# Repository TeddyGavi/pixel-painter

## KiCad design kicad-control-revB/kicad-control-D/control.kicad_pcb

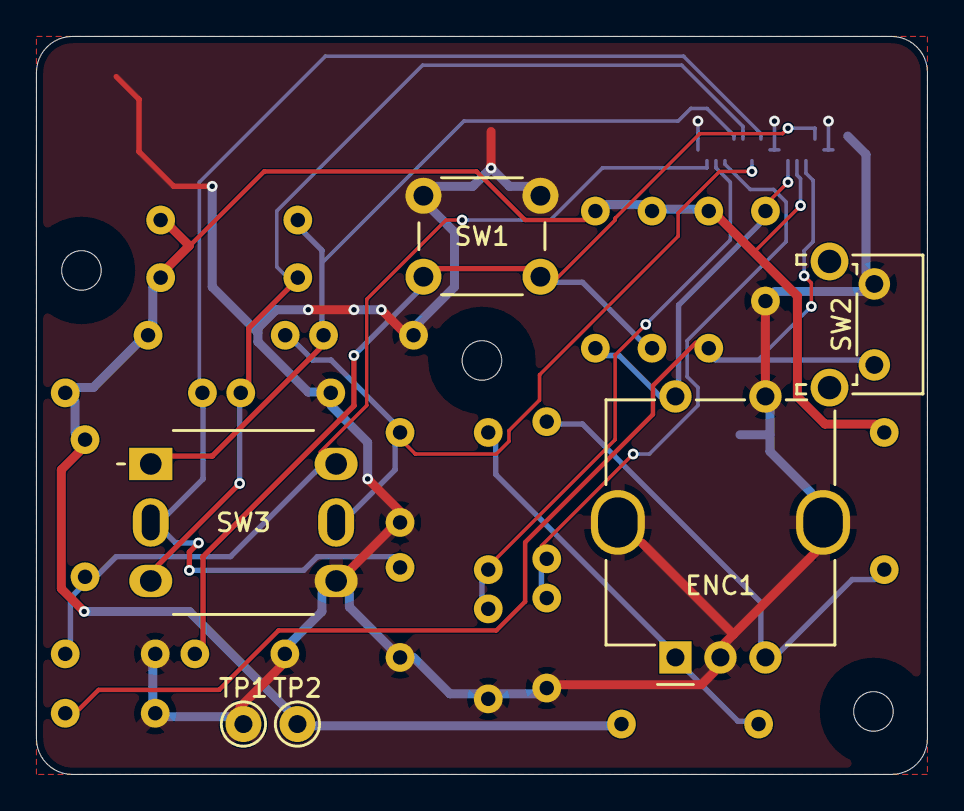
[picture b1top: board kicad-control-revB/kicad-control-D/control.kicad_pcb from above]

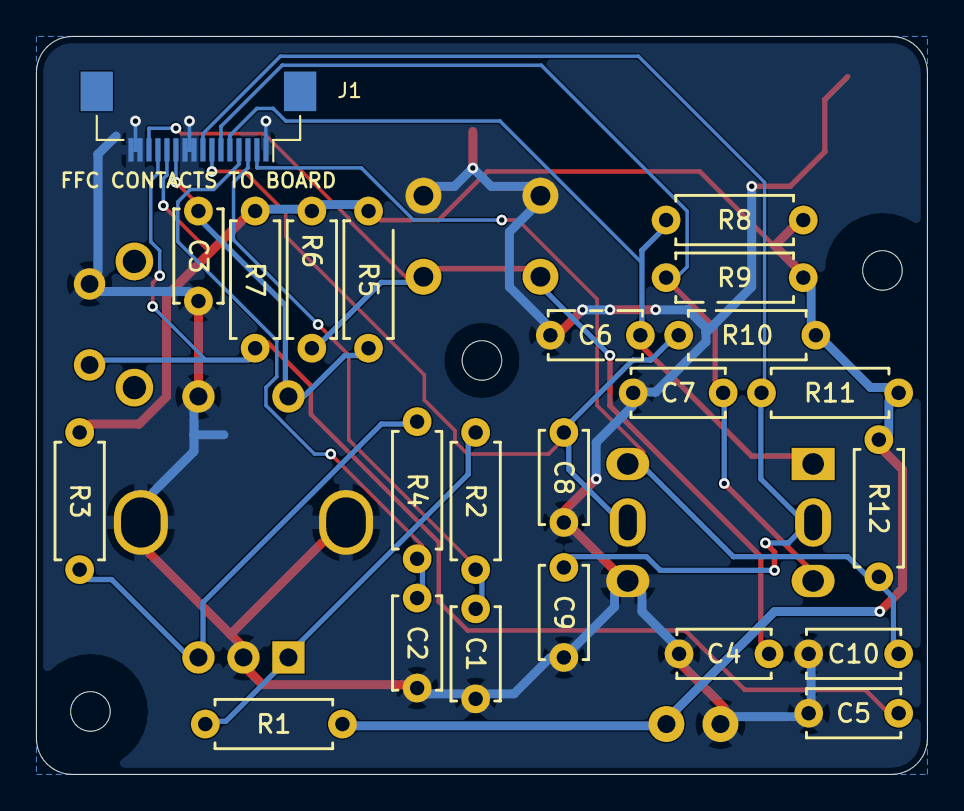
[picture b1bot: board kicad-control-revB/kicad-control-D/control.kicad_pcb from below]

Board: 2 copper layers, 49.5 x 41.0 mm, 32 parts (23 on the bottom side), 14 nets.

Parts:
C1, C2, C3, C4, C5, C6, C7, C8, C9, C10: 10nF; C_Disc_D5.0mm_W2.5mm_P5.00mm
ENC1: PEC11R-4215F-S0024; RotaryEncoder_Bourns_PEC11R-4xxxF-Sxxxx_Vertical
H1, H2, H3: M2; MountingHole_2.2mm_M2
J1: FH12-16S-0.5SH(55); Hirose_FH12-16S-0.5SH_1x16-1MP_P0.50mm_Horizontal
R1, R2, R3, R4, R5, R6, R7, R8, R9, R10, R11, R12: 10k; R_Axial_DIN0207_L6.3mm_D2.5mm_P7.62mm_Horizontal
SW1: B3F-1000 (MENU); SW_PUSH_6mm
SW2: PTS645VL31-2 LFS (SIDE); SW_Tactile_SPST_Angled_PTS645Vx31-2LFS
SW3: SKQUCAA010; SW_Alps_SKQUCAA010_5way_THT
TP1: GND; TestPoint_THTPad_D2.0mm_Drill1.0mm
TP2: 3V3; TestPoint_THTPad_D2.0mm_Drill1.0mm

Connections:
+3V3: J1.12, R1.1, R3.1, R5.1, R6.1, R7.1, R8.1, R9.1, R10.1, R11.1, R12.1, TP2.1
/BTN_MENU: C4.1, J1.14, R6.2, SW1.2
/BTN_SIDE: C5.1, J1.13, R7.2, SW2.2
/ENC_A: C1.1, J1.3, R2.2
/ENC_A_RAW: ENC1.A, R1.2, R2.1
/ENC_B: C2.1, J1.4, R4.2
/ENC_B_RAW: ENC1.B, R3.2, R4.1
/ENC_SW: C3.1, ENC1.S1, J1.11, R5.2
/NAV_C: C10.1, J1.2, R12.2, SW3.6
/NAV_DOWN: C7.1, J1.6, R9.2, SW3.3
/NAV_LEFT: C8.1, J1.7, R10.2, SW3.5
/NAV_RIGHT: C9.1, J1.8, R11.2, SW3.2
/NAV_UP: C6.1, J1.5, R8.2, SW3.1
GND: C1.2, C2.2, C3.2, C4.2, C5.2, C6.2, C7.2, C8.2, C9.2, C10.2, ENC1.C, ENC1.MP, ENC1.S2, J1.1, J1.9, J1.10, J1.15, J1.16, SW1.1, SW2.1, SW3.4, TP1.1

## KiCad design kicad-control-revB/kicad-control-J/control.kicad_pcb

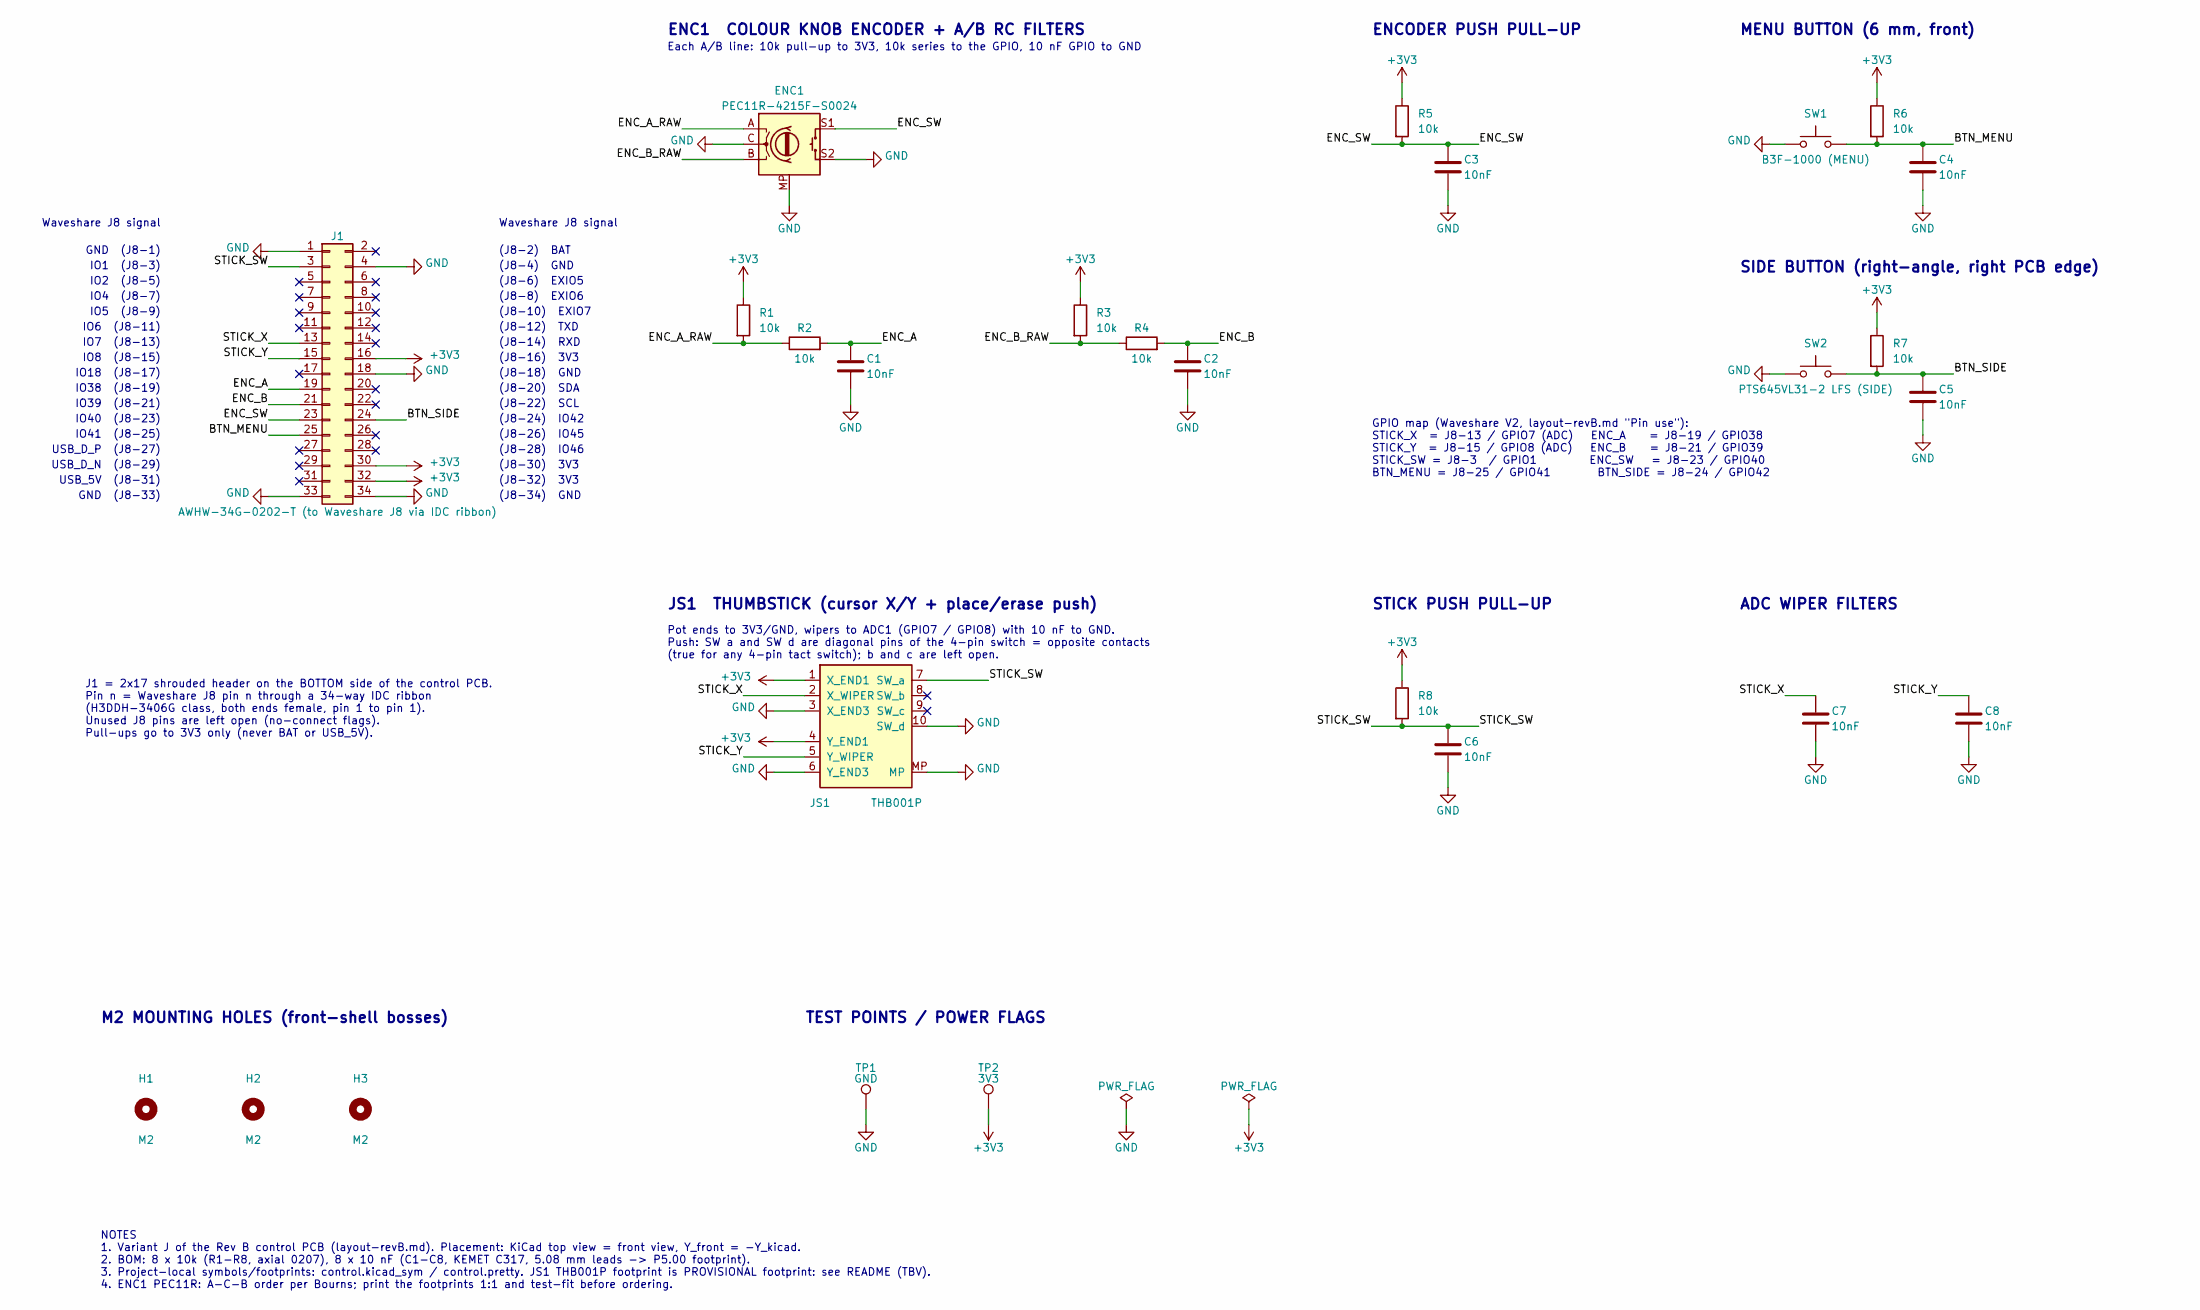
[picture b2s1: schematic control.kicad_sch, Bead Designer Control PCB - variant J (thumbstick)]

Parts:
C1, C2, C3, C4, C5, C6, C7, C8: 10nF; C_Disc_D5.0mm_W2.5mm_P5.00mm; MPN C317C103K5R5TA
ENC1: PEC11R-4215F-S0024; RotaryEncoder_Bourns_PEC11R-4xxxF-Sxxxx_Vertical; MPN PEC11R-4215F-S0024
H1, H2, H3: M2; MountingHole_2.2mm_M2; MPN N/A (PCB hole, M2 screw)
J1: AWHW-34G-0202-T (to Waveshare J8 via IDC ribbon); IDC-Header_2x17_P2.54mm_Vertical; MPN AWHW-34G-0202-T
JS1: THB001P; Joystick_CK_THB001P_PROVISIONAL; MPN THB001P
R1, R2, R3, R4, R5, R6, R7, R8: 10k; R_Axial_DIN0207_L6.3mm_D2.5mm_P7.62mm_Horizontal; MPN MFR-25FRF52-10K
SW1: B3F-1000 (MENU); SW_PUSH_6mm; MPN B3F-1000
SW2: PTS645VL31-2 LFS (SIDE); SW_Tactile_SPST_Angled_PTS645Vx31-2LFS; MPN PTS645VL31-2 LFS
TP1: GND; TestPoint_THTPad_D2.0mm_Drill1.0mm; MPN N/A (bare THT pad)
TP2: 3V3; TestPoint_THTPad_D2.0mm_Drill1.0mm; MPN N/A (bare THT pad)

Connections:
+3V3: J1.16, J1.30, J1.32, JS1.1 (X_END1), JS1.4 (Y_END1), R1.1, R3.1, R5.1, R6.1, R7.1, R8.1, TP2.1
/BTN_MENU: C4.1, J1.25, R6.2, SW1.2
/BTN_SIDE: C5.1, J1.24, R7.2, SW2.2
/ENC_A: C1.1, J1.19, R2.2
/ENC_A_RAW: ENC1.A, R1.2, R2.1
/ENC_B: C2.1, J1.21, R4.2
/ENC_B_RAW: ENC1.B, R3.2, R4.1
/ENC_SW: C3.1, ENC1.S1, J1.23, R5.2
/STICK_SW: C6.1, J1.3, JS1.7 (SW_a), R8.2
/STICK_X: C7.1, J1.13, JS1.2 (X_WIPER)
/STICK_Y: C8.1, J1.15, JS1.5 (Y_WIPER)
GND: C1.2, C2.2, C3.2, C4.2, C5.2, C6.2, C7.2, C8.2, ENC1.C, ENC1.MP, ENC1.S2, J1.1, J1.4, J1.18, J1.33, J1.34, JS1.3 (X_END3), JS1.6 (Y_END3), JS1.10 (SW_d), JS1.MP, SW1.1, SW2.1, TP1.1

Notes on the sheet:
Waveshare J8 signal
GND (J8-1)
(J8-2) BAT
IO1 (J8-3)
(J8-4) GND
IO2 (J8-5)
(J8-6) EXIO5
IO4 (J8-7)
(J8-8) EXIO6
IO5 (J8-9)
(J8-10) EXIO7
IO6 (J8-11)
(J8-12) TXD
IO7 (J8-13)
(J8-14) RXD
IO8 (J8-15)
(J8-16) 3V3
IO18 (J8-17)
(J8-18) GND
IO38 (J8-19)
(J8-20) SDA
IO39 (J8-21)
(J8-22) SCL
IO40 (J8-23)
(J8-24) IO42
IO41 (J8-25)
(J8-26) IO45
USB_D_P (J8-27)
(J8-28) IO46
USB_D_N (J8-29)
(J8-30) 3V3
USB_5V (J8-31)
(J8-32) 3V3
GND (J8-33)
(J8-34) GND
J1 = 2x17 shrouded header on the BOTTOM side of the control PCB. Pin n = Waveshare J8 pin n through a 34-way IDC ribbon (H3DDH-3406G class, both ends female, pin 1 to pin 1). Unused J8 pins are left open (no-connect flags). Pull-ups go to 3V3 only (never BAT or USB_5V).
ENC1 COLOUR KNOB ENCODER + A/B RC FILTERS
Each A/B line: 10k pull-up to 3V3, 10k series to the GPIO, 10 nF GPIO to GND
ENCODER PUSH PULL-UP
MENU BUTTON (6 mm, front)

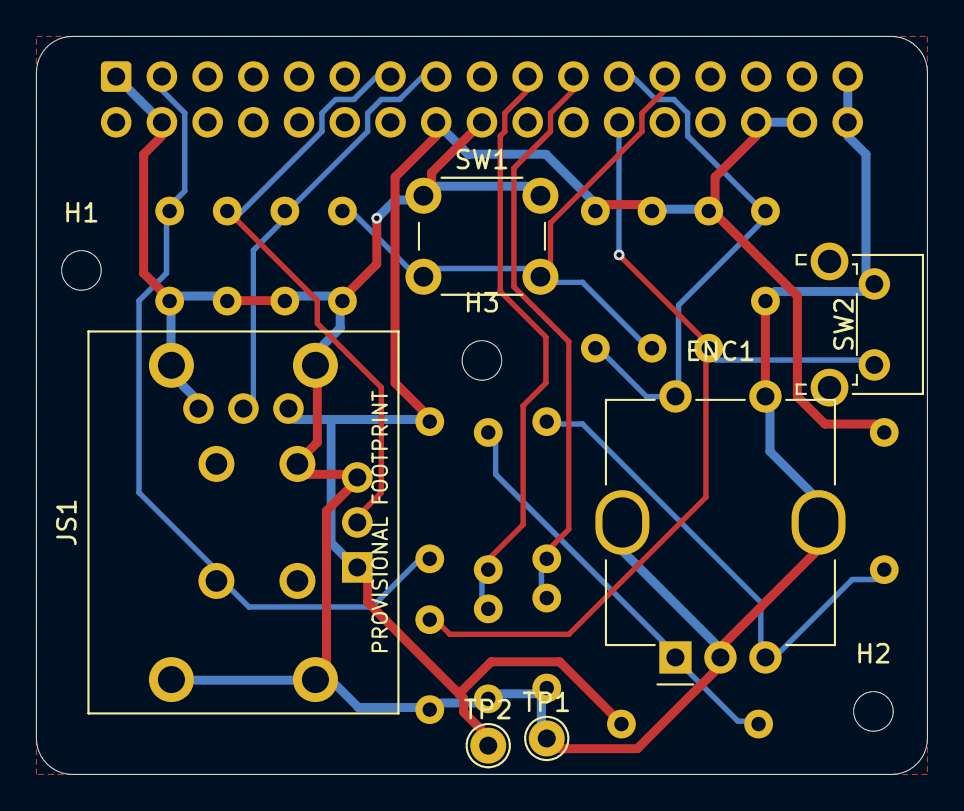
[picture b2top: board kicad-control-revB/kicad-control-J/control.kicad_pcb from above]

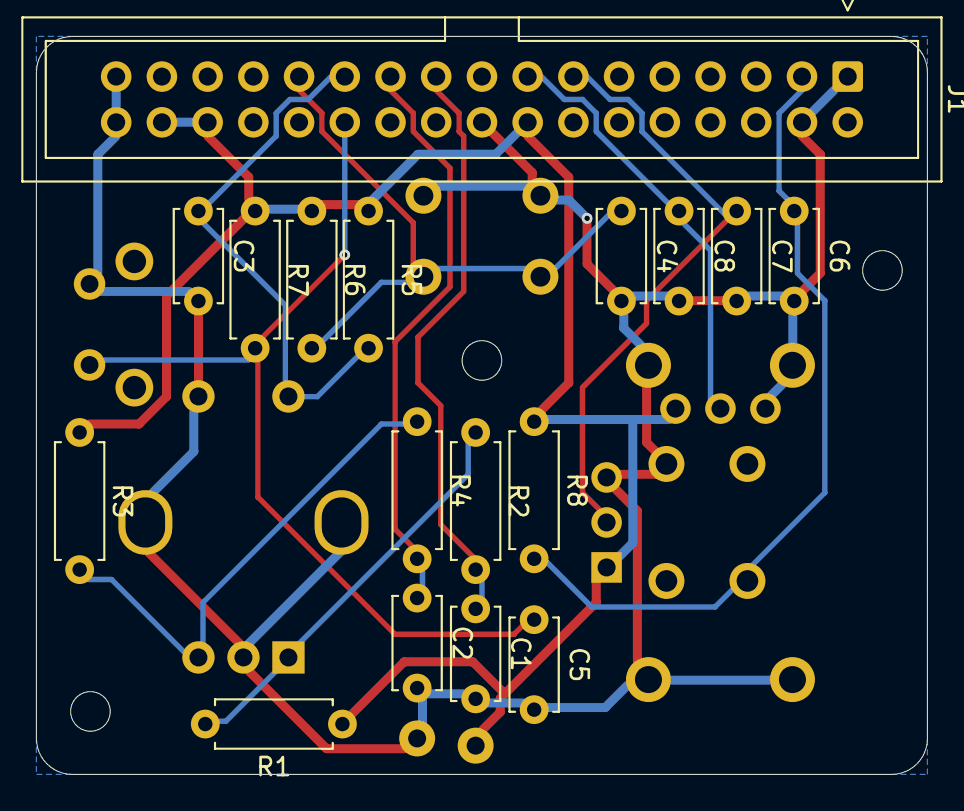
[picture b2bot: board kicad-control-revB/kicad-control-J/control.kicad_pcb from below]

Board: 2 copper layers, 49.5 x 41.0 mm, 26 parts (17 on the bottom side), 12 nets.

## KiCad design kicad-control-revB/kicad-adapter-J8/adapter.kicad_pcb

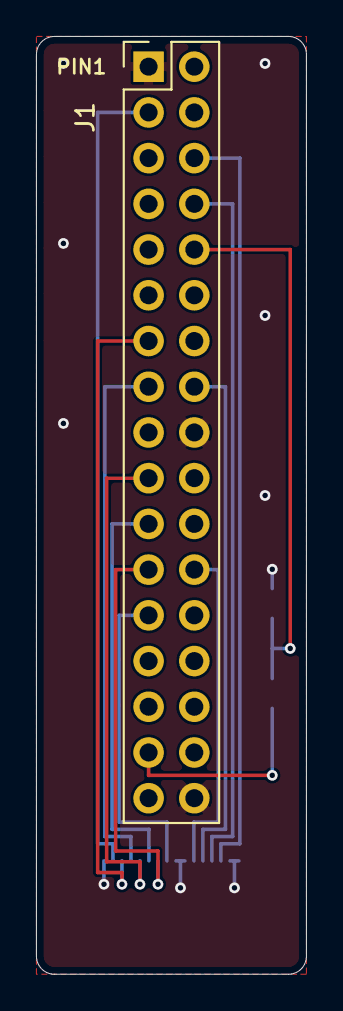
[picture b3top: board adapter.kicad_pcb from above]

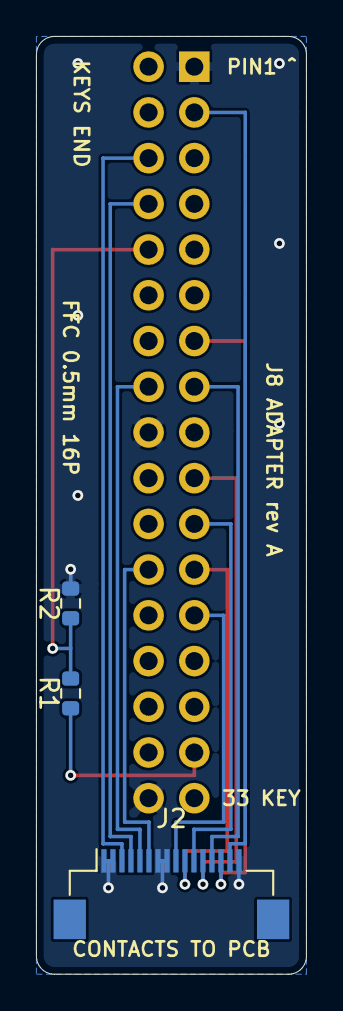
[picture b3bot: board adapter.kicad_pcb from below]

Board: 2 copper layers, 15.0 x 52.1 mm, 4 parts (3 on the bottom side), 14 nets.

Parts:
J1: 2x17 male 2.54 (into Waveshare J8); PinHeader_2x17_P2.54mm_Vertical
J2: FH12-16S-0.5SH(55); Hirose_FH12-16S-0.5SH_1x16-1MP_P0.50mm_Horizontal
R1: 2.2k; R_0603_1608Metric
R2: 4.7k; R_0603_1608Metric

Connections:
+3V3: J1.16, J2.5
/BTN_MENU: J1.6, J2.3
/BTN_SIDE: J1.8, J2.4
/ENC_A: J1.13, J2.14
/ENC_B: J1.15, J2.13
/ENC_SW: J1.24, J2.6
/NAV_C: J1.3, J2.15
/NAV_DOWN: J1.21, J2.11
/NAV_LEFT: J1.23, J2.10
/NAV_RIGHT: J1.25, J2.9
/NAV_UP: J1.19, J2.12
/USB_5V: J1.31, R1.1
/USB_PRESENT: J1.10, R1.2, R2.1
GND: J1.1, J1.18, J1.34, J2.1, J2.2, J2.7, J2.8, J2.16, R2.2

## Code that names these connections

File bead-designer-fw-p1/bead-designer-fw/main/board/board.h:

#pragma once
// Board abstraction. Everything hardware-specific lives behind this header.
// board_ws241.c  : Waveshare ESP32-S3-Touch-AMOLED-2.41 V2 (product, pins VERIFIED
//                  against the V2 schematic, spec Rev A.5 section 5.1)
// board_freenove.c: Freenove ESP32 CYD 2.4" (interim, pins TBV)

#include <stdint.h>
#include <stdbool.h>
#include "sdkconfig.h"   // CONFIG_IDF_TARGET_* used below

// Inputs (all switches active low): a 5-way D-pad (cursor; centre = erase,
// long-press = eyedropper), one push-encoder (turn = colour slot, press = place,
// press-and-turn = browse the catalogue), MENU and SIDE. -1 = not wired.
#if CONFIG_IDF_TARGET_ESP32S3
// ---- Waveshare 2.41 V2 + Rev B control board, D variant (layout-revB.md),
//      via header J8 ----
#define PIN_DPAD_UP     38  // J8-19
#define PIN_DPAD_DOWN   39  // J8-21 (MTCK: no external JTAG while in use)
// LEFT/RIGHT are deliberately crossed against the PCB net names. Alps SKQUCAA010
// top view: B (pin 2) = LEFT, D (pin 5) = RIGHT, but control PCB Rev B wires
// pad 2 to net NAV_RIGHT (J8-25) and pad 5 to NAV_LEFT (J8-23). Fixed here
// rather than respinning the board (2026-11-15).
#define PIN_DPAD_LEFT   41  // J8-25, net NAV_RIGHT = SW3 pin 2 (B, physical left)
#define PIN_DPAD_RIGHT  40  // J8-23, net NAV_LEFT  = SW3 pin 5 (D, physical right)
#define PIN_DPAD_CENTER 1   // J8-3
#define PIN_ENC_A       7   // J8-13
#define PIN_ENC_B       8   // J8-15
#define PIN_ENC_SW      42  // J8-24
#define PIN_BTN_MENU    (-1) // on the TCA9554 expander instead: EXIO_BTN_MENU
#define PIN_BTN_SIDE    (-1) // on the TCA9554 expander instead: EXIO_BTN_SIDE
#define EXIO_BTN_MENU   5    // TCA9554 P5 (J8-6), polled over I2C by input.c
#define EXIO_BTN_SIDE   6    // TCA9554 P6 (J8-8)
#define EXIO_USB_PRESENT 7   // TCA9554 P7 (J8-10): high = USB 5 V present (R1 2.2k / R2 4.7k divider on the J8 adapter PCB, rev A). Not read yet; debounce ~100 ms
#define PIN_DPAD_LADDER (-1) // D-pad uses its own GPIOs here
#define PIN_PWR_KEY     15  // onboard PWR key (Key_BAT)
#define PIN_PWR_LATCH   16  // BAT_Control: drive HIGH at boot or battery power drops
#define PIN_BAT_ADC     17  // battery voltage / 3 (200k/100k divider)
#define HAVE_PWR_LATCH  1
#define DISPLAY_W       450 // native RM690B0 panel px (UI update stage 1, 2026-11-20; was 225 logical px doubled)
#define DISPLAY_ROT180  1   // panel is mounted upside down relative to the case (USB-C left): flip in the flush (checked on the board 2026-11-17)
#define DISPLAY_H       600
#define SAVER_W         225 // the screen saver keeps its 225x300 bitmap, each px shown 2x2
#define SAVER_H         300
#define UI_HIRES        1   // native-resolution UI: Soft-bead art, Chicago 3x Scale3x (docs/ui-update-2.41)
#elif CONFIG_IDF_TARGET_ESP32
// ---- Freenove FNK0114A 2.4" ST7789 (ESP32-WROOM-32E), from Freenove's
//      2.4inch_ESP32-32E_Display_Schematic.pdf. Only 2 free GPIOs exist. ----
// Breadboard bench wiring (BENCH.md). Only 5 GPIOs reach connectors, so the
// 5-way D-pad is a resistor ladder on one ADC pin. P3 = the SD-card bus: no card.
#define PIN_DPAD_UP     (-1) // all 5 directions: ladder on PIN_DPAD_LADDER
#define PIN_DPAD_DOWN   (-1)
#define PIN_DPAD_LEFT   (-1)
#define PIN_DPAD_RIGHT  (-1)
#define PIN_DPAD_CENTER (-1)
#define PIN_DPAD_LADDER 27   // P3 pin 4: ADC2_CH7 (unreadable while Wi-Fi runs)
#define PIN_ENC_A       35   // P4 pin 2; input-only, EXTERNAL 10k pull-up required
#define PIN_ENC_B       23   // P3 pin 1 (SPI_MOSI)
#define PIN_ENC_SW      19   // P3 pin 2 (SPI_MISO)
#define PIN_BTN_MENU    18   // P3 pin 3 (SPI_CLK)
#define PIN_BTN_SIDE    0    // onboard BOOT key (10k pull-up); don't hold it during reset
#define EXIO_USB_PRESENT (-1) // no USB sense on the Freenove
#define EXIO_BTN_MENU   (-1) // no I/O expander on the Freenove
#define EXIO_BTN_SIDE   (-1)
#define PIN_PWR_KEY     (-1)
#define PIN_PWR_LATCH   (-1)
#define PIN_BAT_ADC     34   // 100k/100k divider (x2)
// Display (ST7789, HSPI): MOSI 13, SCLK 14, CS 15, DC 2, RST tied to EN, BL 21 (high = on)
#define LCD_MOSI 13
#define LCD_SCLK 14
#define LCD_CS   15
#define LCD_DC   2
#define LCD_BL   21
#define HAVE_PWR_LATCH  0
#define DISPLAY_W       240 // portrait
#define DISPLAY_H       320
#define SAVER_W         DISPLAY_W
#define SAVER_H         DISPLAY_H
#define UI_HIRES        0
#endif

// Display operations each board implements.
typedef struct {
    void (*init)(void);
    // Fill an axis-aligned rectangle with one RGB565 colour (portrait coords).
    void (*fill_rect)(int x, int y, int w, int h, uint16_t rgb565);
    // Push a small RGB565 bitmap (glyphs, icons).
    void (*blit)(int x, int y, int w, int h, const uint16_t *px);
    void (*set_brightness)(uint8_t pct); // burn-in care: dim chrome, sleep idle
    // Optional (NULL = draws go straight to the panel): send everything drawn since
    // the last call in one go, so a screen change appears at once (no flicker).
    void (*present)(void);
} display_ops_t;

const display_ops_t *board_display(void);
void board_early_init(void);   // power latch FIRST, then rails/quirks
int  board_battery_mv(void);   // battery voltage (calibrated, averaged), -1 if unsupported/unreadable
// Switch off: drop the power latch. Where that can't cut power (USB connected, or
// a board without a latch) fall back to a "soft off": display off, deep sleep,
// woken by the PWR key as a fresh boot. Does not return.
void board_power_off(void);
void board_display_sleep(bool sleep); // panel off (low power) / back on; redraw after waking
int  board_exio_read(void);
const char *board_status(void); // one-line hardware status (reprinted by serial '?')    // I/O expander input port (bit n = EXIOn), -1 if none
// Test support: the shadow framebuffer (DISPLAY_W x DISPLAY_H, big-endian RGB565),
// or NULL on boards without one. Hold board_fb_lock(true) while reading it.
const uint16_t *board_framebuffer(void);
void board_fb_lock(bool lock);
// The same framebuffer for drawing into directly (menu rows), or NULL. Hold
// board_fb_lock(true) while writing and mark the area with board_fb_dirty.
uint16_t *board_fb_draw(void);
// After writing into the framebuffer directly (screen saver): mark the area changed.
void board_fb_dirty(int x, int y, int w, int h);
// Two-colour bitmap mode (screen saver): returns a cleared 1-bit-per-pixel bitmap
// (SAVER_W x SAVER_H, (SAVER_W+7)/8 bytes per row, bit x&7 of byte x>>3) shown in
// fg/bg, or NULL if the board has none. Mark changes with board_fb_dirty (under
// board_fb_lock); while the bitmap is on, board_fb_dirty takes SAVER coordinates.
uint8_t *board_mono_begin(uint16_t fg, uint16_t bg);
void board_mono_color(uint16_t fg, uint16_t bg);
void board_mono_end(void);
void board_fb_sync(void);      // test dump: bring the framebuffer up to date first
// Touch (FT6336U on the Waveshare; none on the Freenove). board_touch_power(true)
// resets the controller (first report ~300 ms later); false puts it in hibernate.
// Returns false if the controller did not answer. board_touch_read: 1 = a finger at
// (*x, *y) in display coordinates, 0 = no finger, -1 = no controller / read failed.
bool board_touch_power(bool on);
int  board_touch_read(int *x, int *y);
